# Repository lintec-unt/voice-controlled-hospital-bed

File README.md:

# Voice Controlled Hospital Bed System 1.0

This is the version 1.0 of the Voice Controlled Hospital Bed System. This proyect aims to allow bedridden patients that have a discapacity that do not allow them to use their hands to control the position of their bed, but they can talk, to control the bed with oral commands.

In this first version, the system can only work with a particular model of hospital bed (Pettinari PM Millennium), and it works with a PC with a speech recognition software (for example, Windows Speech Recognition, Dragon NaturallySpeaking, among others).

The system has the following parts:

* PC with Microsoft Windows OS and a speech recognition software.
* PC software to control the hospital bed.
* Arduino UNO board that translates the commands from the PC to actions in the bed.
* An Arduino shield that has all the extra hardware needed.
* A case to put the Arduino board and its shield to adapt it in the bed.

In this repository, we have uploaded the codes and files of:

* Code of the PC software to control the hospital bed.
* Code of the Arduino UNO board.
* PCB design of the Arduino shield.
* A STL file of the case.

### Arduino shield (PCB folder)

The arduino UNO board is connected to the hospital bed by the communication port for the wired remote control command. To emulate the buttons of the remote control, we used the GPIO port. As we intended to avoid electrical connection between the Arduino board (and the PC in upstream connection), the connections with the bed and the GPIO ports are between optocouplers. After the optocouplers, there is DIN connector (DIN 41524) that is connected in the bed. the connection between the PC and the Arduino board is by the means of the USB serial port.

The PCB design (the PCB folder) includes the optocouplers and a connector for the cable with the DIN connection.

### Arduino Board Software (ArduinoCode folder)

It was developed under Arduino IDE and with the standard libraries from Arduino.cc

This software has the typical infinite loop structure (setup() and loop()). In setup(), it starts all the GPIO pin needed as inputs and wait a command from the PC to start working. In loop(), the Arduino receive a char, and if it means a valid command, it activates the corresponding GPIO pin.

### The case (STL folder)

The arduino board and its shield was attached in the hospital bed by a 3d printed case. This case works as kind of protection for all the electronics.  

### The PC sofware (PCSoftwareCode folder)

The software that send the commands to the arduino is coded in C#, it was coded under Visual Studio IDE 15.

When the software is initializated, it search for the Arduino board in the differents avalaible serial ports (COM ports). To find it, it sends a char that the Arduino undestand as valid one and the Arduino responds with another char. The main windows has all the commands to move the bed in the form of images. If the user does a click in one of them, the software sends the correponding command to the Arduino to move the bed every 500 ms (this delta of time assures a smooth movement of the bed). To stop the movement, it is necesary to click in the same image but also, the software automatically stop the movement after 30 seconds.

The user using the speech recognition software can send a voice command to make click in one of the images. The size of the images are intended to make easier to the user to choose one of the images.

## Roadmap

For new advances in this work, we want to add the support for other models and brand of hospital beds. Also, we want adding the posibility to replace the PC with a embebbed system with a buit-in speech recognition software.

We are open to new ideas, everyone is open to participate in this development, as long as the guidelines are respected (see Contributing.md)

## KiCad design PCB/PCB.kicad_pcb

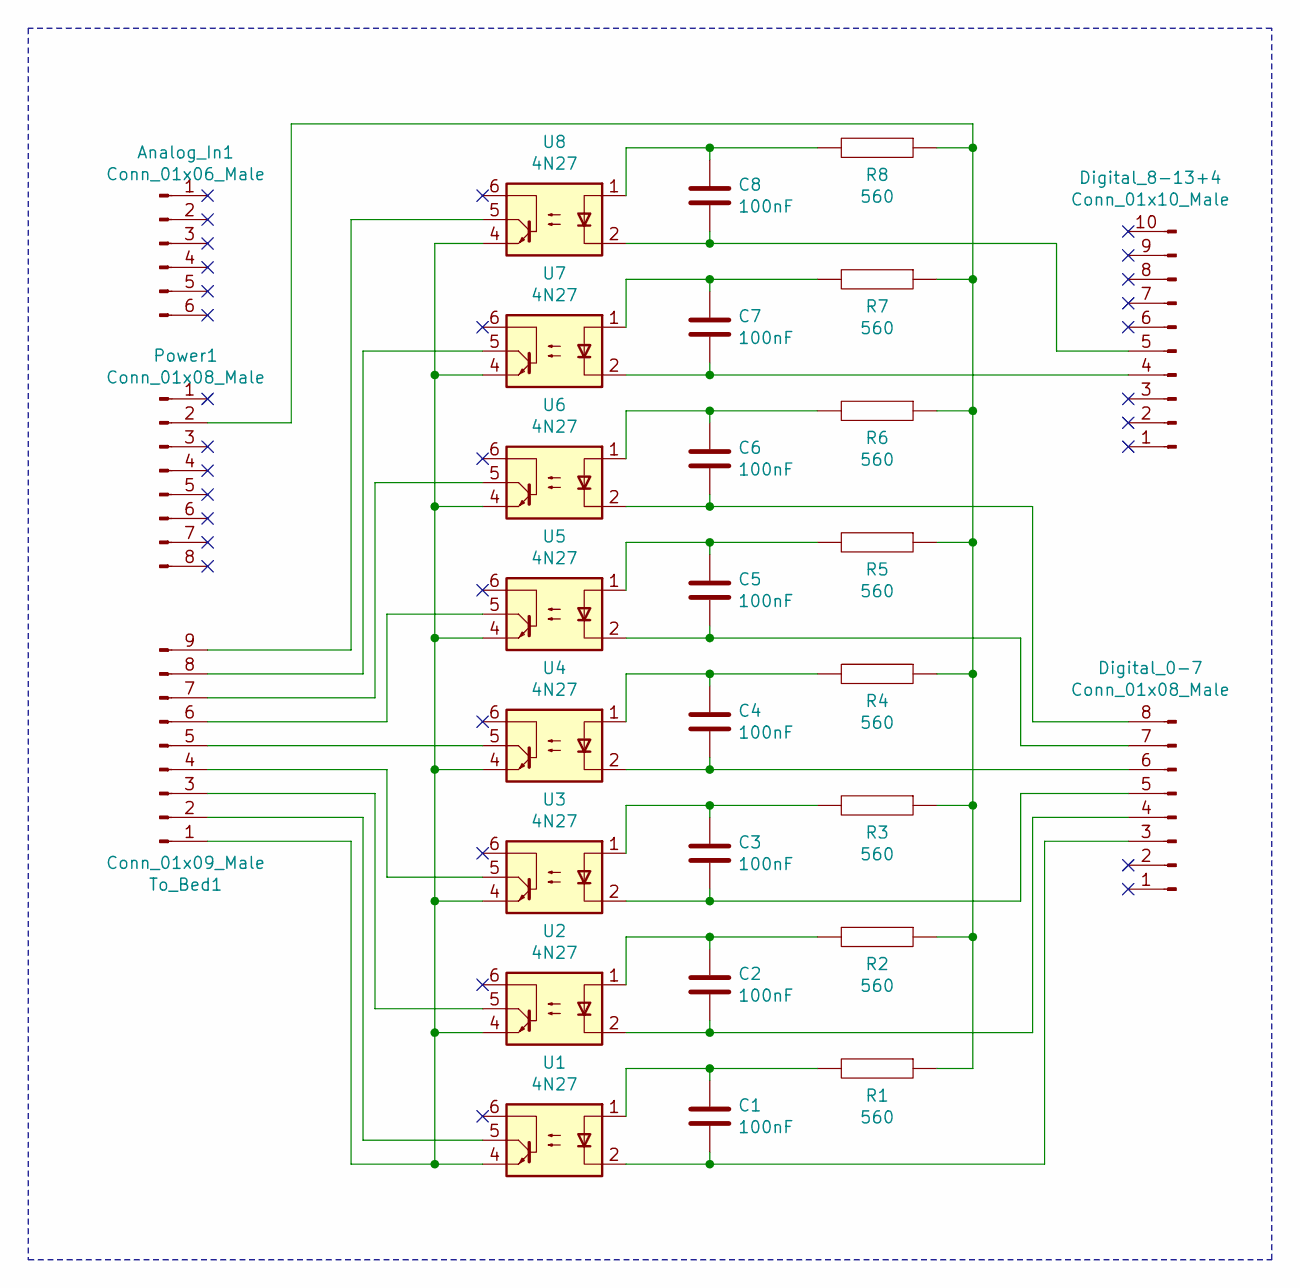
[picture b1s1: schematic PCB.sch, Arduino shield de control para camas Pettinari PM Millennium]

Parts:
Analog_In1: Conn_01x06_Male; PinHeader_1x06_P2.54mm_Vertical
C1, C2, C3, C4, C5, C6, C7, C8: 100nF; C_Disc_D6.0mm_W2.5mm_P5.00mm
Digital_0-7: Conn_01x08_Male; PinHeader_1x08_P2.54mm_Vertical
Digital_8-13+4: Conn_01x10_Male; PinHeader_1x10_P2.54mm_Vertical
Power1: Conn_01x08_Male; PinHeader_1x08_P2.54mm_Vertical
R1, R2, R3, R4, R5, R6, R7, R8: 560; R_Axial_DIN0207_L6.3mm_D2.5mm_P7.62mm_Horizontal
To_Bed1: Conn_01x09_Male; PinHeader_1x09_P2.54mm_Vertical
U1, U2, U3, U4, U5, U6, U7, U8: 4N27; DIP-6_W7.62mm

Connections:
unnamed: C1.1, R1.2, U1.1
unnamed: C1.2, Digital_0-7.3, U1.2
unnamed: C2.1, R2.2, U2.1
unnamed: C2.2, Digital_0-7.4, U2.2
unnamed: C3.1, R3.2, U3.1
unnamed: C3.2, Digital_0-7.5, U3.2
unnamed: C4.1, R4.2, U4.1
unnamed: C4.2, Digital_0-7.6, U4.2
unnamed: C5.1, R5.2, U5.1
unnamed: C5.2, Digital_0-7.7, U5.2
unnamed: C6.1, R6.2, U6.1
unnamed: C6.2, Digital_0-7.8, U6.2
unnamed: C7.1, R7.2, U7.1
unnamed: C7.2, Digital_8-13+4.4, U7.2
unnamed: C8.1, R8.2, U8.1
unnamed: C8.2, Digital_8-13+4.5, U8.2
unnamed: Power1.2, R1.1, R2.1, R3.1, R4.1, R5.1, R6.1, R7.1, R8.1
unnamed: To_Bed1.1, U1.4, U2.4, U3.4, U4.4, U5.4, U6.4, U7.4, U8.4
unnamed: To_Bed1.2, U1.5
unnamed: To_Bed1.3, U2.5
unnamed: To_Bed1.4, U3.5
unnamed: To_Bed1.5, U4.5
unnamed: To_Bed1.6, U5.5
unnamed: To_Bed1.7, U6.5
unnamed: To_Bed1.8, U7.5
unnamed: To_Bed1.9, U8.5

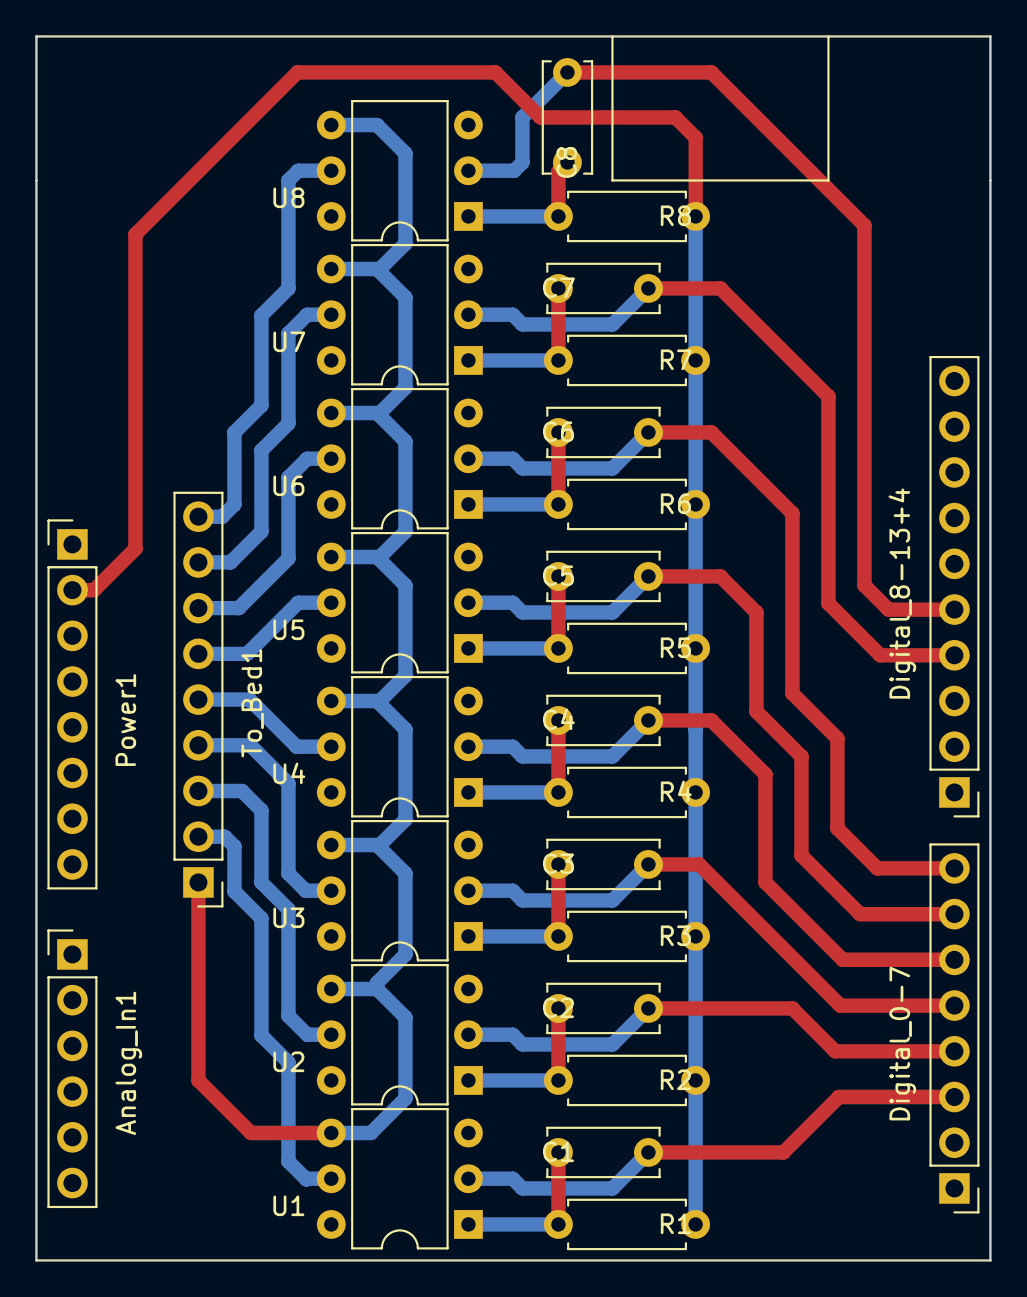
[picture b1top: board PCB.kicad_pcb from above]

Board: 2 copper layers, 53.0 x 68.0 mm, 29 parts (0 on the bottom side), 26 nets.

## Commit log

2019-11-20 Add LICENSE
2019-11-20 Add CONTRIBUTING
2019-11-21 First uploaded of the code
2019-11-21 modified README.md
2019-11-21 README.md
2019-11-21 Removed images from README.md

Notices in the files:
PCB/PCB.kicad_pcb:
Copyright (c) 2019, CONICET, UNT, SIPROSA
